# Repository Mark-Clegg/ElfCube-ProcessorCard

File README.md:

# Elf-Cube - Processor card
Simple retro computer based on the 1802 series of processors.

Holds the main CPU, 1 x 32K ROM and 2 x 32K RAM sockets.

After reset, ROM runs from 0x0000 - 0x7FFF and RAM from 0x8000 - 0xFFFF. As soon as an instruction fetch occurs from RAM, the
ROM is replaced with the second RAM chip leaving a full 64K RAM available to user programs.

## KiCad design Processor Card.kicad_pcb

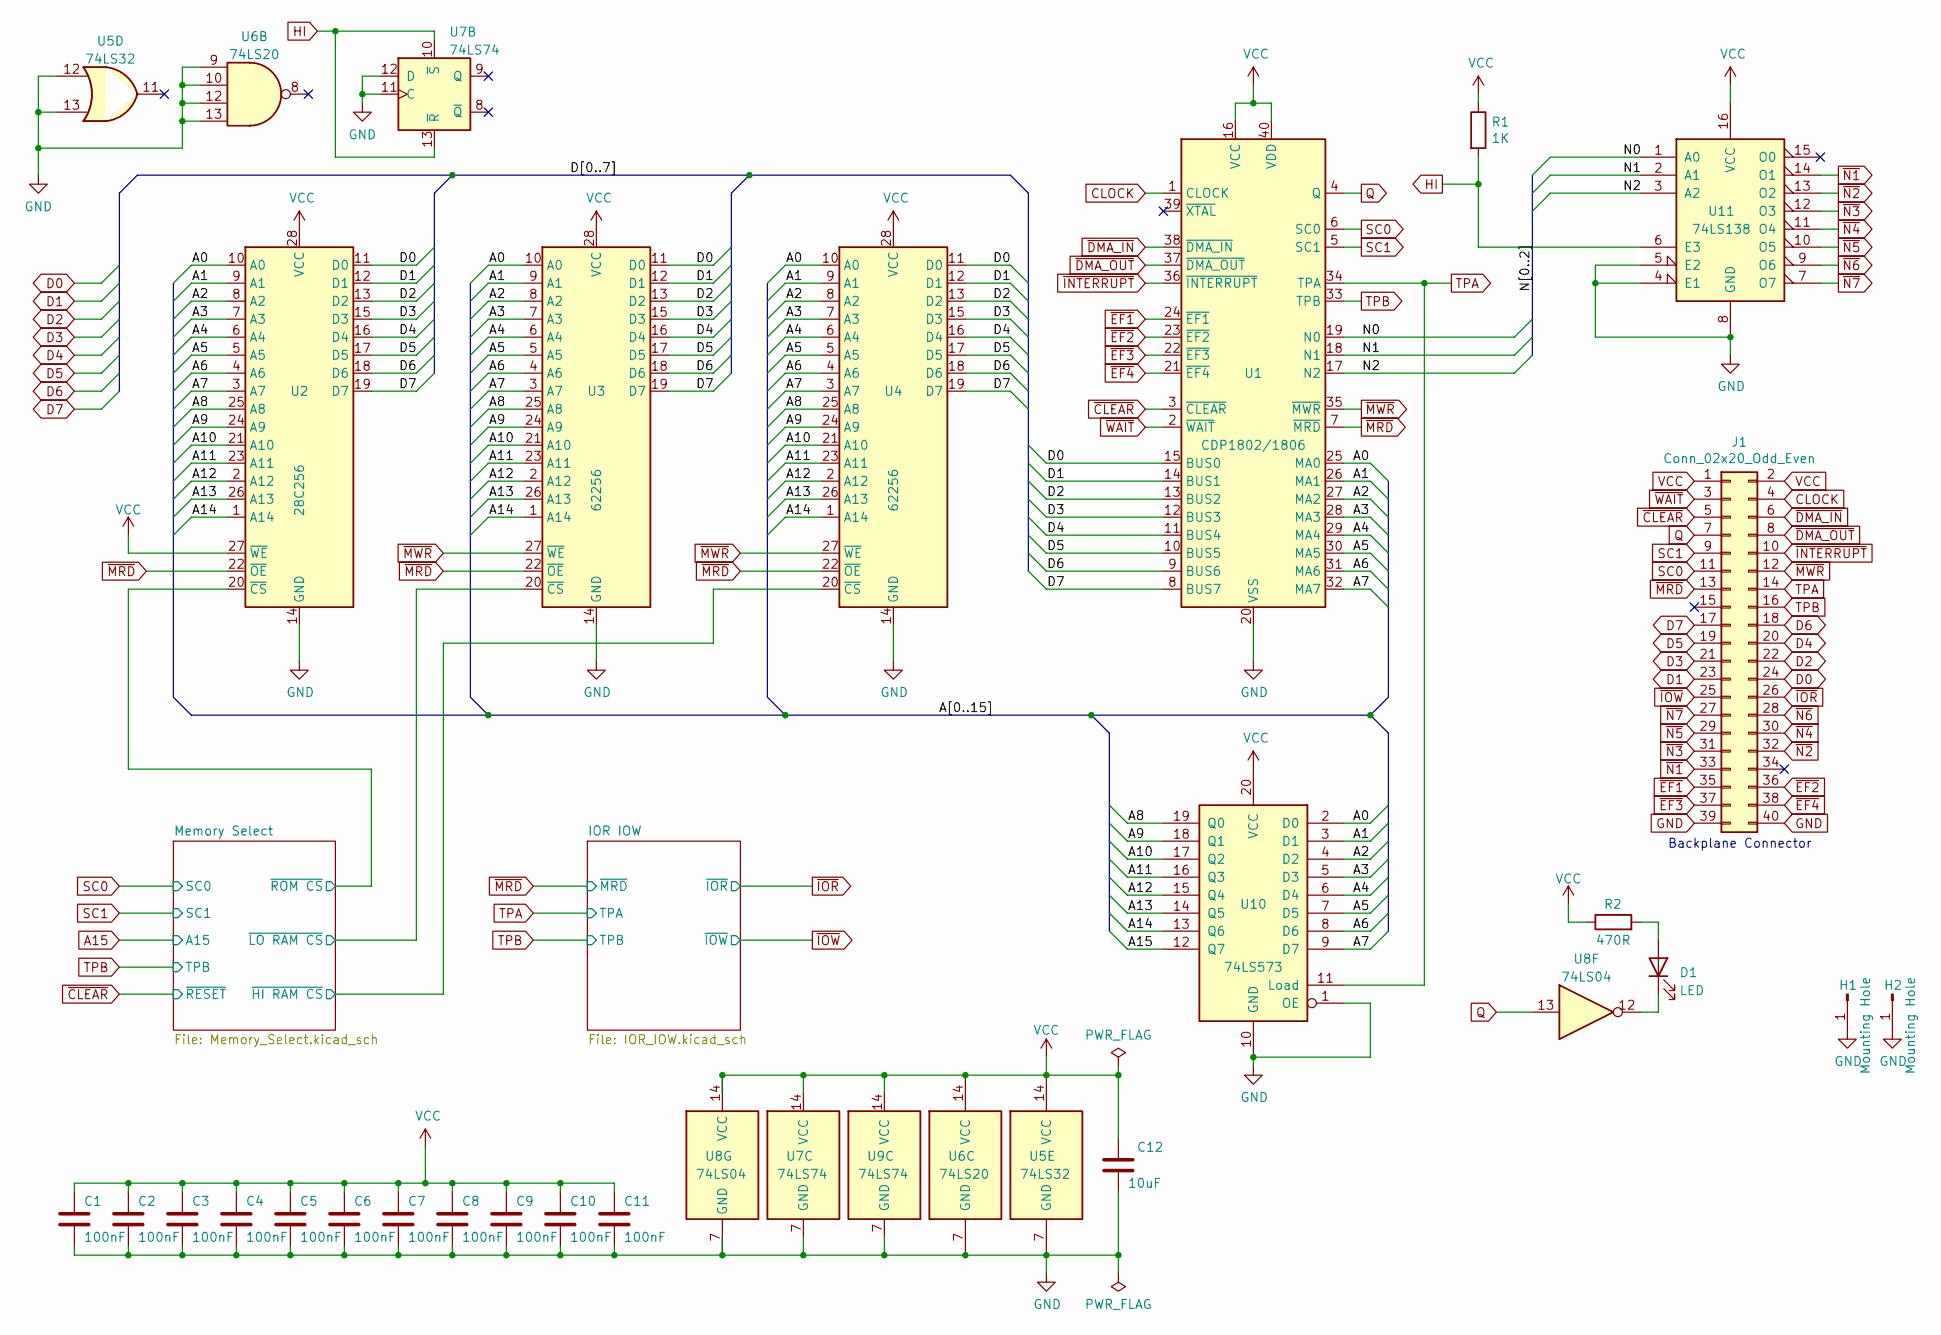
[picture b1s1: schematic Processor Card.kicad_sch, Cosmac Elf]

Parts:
C1, C2, C3, C4, C5, C6, C7, C8, C9, C10, C11: 100nF; C_Disc_D3.8mm_W2.6mm_P2.50mm
C12: 10uF; CP_Radial_D5.0mm_P2.50mm
D1: LED; LED_D3.0mm_Horizontal_O1.27mm_Z2.0mm
H1, H2: Mounting Hole; MountingHole_3.2mm_M3_Pad_Via
J1: Conn_02x20_Odd_Even; PinHeader_2x20_P2.54mm_Horizontal
R1: 1K; R_Axial_DIN0207_L6.3mm_D2.5mm_P7.62mm_Horizontal
R2: 470R; R_Axial_DIN0207_L6.3mm_D2.5mm_P7.62mm_Horizontal
U1: CDP1802/1806; DIP-40_W15.24mm_Socket
U2: 28C256; DIP-28_W15.24mm_Socket
U3, U4: 62256; DIP-28_W15.24mm_Socket
U5: 74LS32; DIP-14_W7.62mm
U6: 74LS20; DIP-14_W7.62mm
U7, U9: 74LS74; DIP-14_W7.62mm
U8: 74LS04; DIP-14_W7.62mm
U10: 74LS573; DIP-20_W7.62mm
U11: 74LS138; DIP-16_W7.62mm

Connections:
/A0: U1.25 (MA0), U2.10 (A0), U3.10 (A0), U4.10 (A0), U10.2 (D0)
/A1: U1.26 (MA1), U2.9 (A1), U3.9 (A1), U4.9 (A1), U10.3 (D1)
/A2: U1.27 (MA2), U2.8 (A2), U3.8 (A2), U4.8 (A2), U10.4 (D2)
/A3: U1.28 (MA3), U2.7 (A3), U3.7 (A3), U4.7 (A3), U10.5 (D3)
/A4: U1.29 (MA4), U2.6 (A4), U3.6 (A4), U4.6 (A4), U10.6 (D4)
/A5: U1.30 (MA5), U2.5 (A5), U3.5 (A5), U4.5 (A5), U10.7 (D5)
/A6: U1.31 (MA6), U2.4 (A6), U3.4 (A6), U4.4 (A6), U10.8 (D6)
/A7: U1.32 (MA7), U2.3 (A7), U3.3 (A7), U4.3 (A7), U10.9 (D7)
/A8: U2.25 (A8), U3.25 (A8), U4.25 (A8), U10.19 (Q0)
/A9: U2.24 (A9), U3.24 (A9), U4.24 (A9), U10.18 (Q1)
/A10: U2.21 (A10), U3.21 (A10), U4.21 (A10), U10.17 (Q2)
/A11: U2.23 (A11), U3.23 (A11), U4.23 (A11), U10.16 (Q3)
/A12: U2.2 (A12), U3.2 (A12), U4.2 (A12), U10.15 (Q4)
/A13: U2.26 (A13), U3.26 (A13), U4.26 (A13), U10.14 (Q5)
/A14: U2.1 (A14), U3.1 (A14), U4.1 (A14), U10.13 (Q6)
/Memory Select/~HI RAM CS: U4.20 (~CS); also elsewhere on the board
/Memory Select/~LO RAM CS: U3.20 (~CS); also elsewhere on the board
/Memory Select/~ROM CS: U2.20 (~CS); also elsewhere on the board
/N0: U1.19 (N0), U11.1 (A0)
/N1: U1.18 (N1), U11.2 (A1)
/N2: U1.17 (N2), U11.3 (A2)
A15: U10.12 (Q7); also elsewhere on the board
CLOCK: J1.4, U1.1 (CLOCK)
D0: J1.24, U1.15 (BUS0), U2.11 (D0), U3.11 (D0), U4.11 (D0)
D1: J1.23, U1.14 (BUS1), U2.12 (D1), U3.12 (D1), U4.12 (D1)
D2: J1.22, U1.13 (BUS2), U2.13 (D2), U3.13 (D2), U4.13 (D2)
D3: J1.21, U1.12 (BUS3), U2.15 (D3), U3.15 (D3), U4.15 (D3)
D4: J1.20, U1.11 (BUS4), U2.16 (D4), U3.16 (D4), U4.16 (D4)
D5: J1.19, U1.10 (BUS5), U2.17 (D5), U3.17 (D5), U4.17 (D5)
D6: J1.18, U1.9 (BUS6), U2.18 (D6), U3.18 (D6), U4.18 (D6)
D7: J1.17, U1.8 (BUS7), U2.19 (D7), U3.19 (D7), U4.19 (D7)
GND: C1.2, C2.2, C3.2, C4.2, C5.2, C6.2, C7.2, C8.2, C9.2, C10.2, C11.2, C12.2, H1.1, H2.1, J1.39, J1.40, U1.20 (VSS), U2.14 (GND), U3.14 (GND), U4.14 (GND), U5.7 (GND), U5.12, U5.13, U6.7 (GND), U6.9, U6.10, U6.12, U6.13, U7.7 (GND), U7.11 (C), U7.12 (D), U8.7 (GND), U9.7 (GND), U10.1 (OE), U10.10 (GND), U11.4 (E1), U11.5 (E2), U11.8 (GND); also elsewhere on the board
HI: R1.2, U7.10 (~S), U7.13 (~R), U11.6 (E3); also elsewhere on the board
unnamed: D1.1 (K), U8.12
unnamed: D1.2 (A), R2.2
Q: J1.7, U1.4 (Q), U8.13
SC0: J1.11, U1.6 (SC0); also elsewhere on the board
SC1: J1.9, U1.5 (SC1); also elsewhere on the board
TPA: J1.14, U1.34 (TPA), U10.11 (Load); also elsewhere on the board
TPB: J1.16, U1.33 (TPB); also elsewhere on the board
VCC: C1.1, C2.1, C3.1, C4.1, C5.1, C6.1, C7.1, C8.1, C9.1, C10.1, C11.1, C12.1, J1.1, J1.2, R1.1, R2.1, U1.16 (VCC), U1.40 (VDD), U2.27 (~WE), U2.28 (VCC), U3.28 (VCC), U4.28 (VCC), U5.14 (VCC), U6.14 (VCC), U7.14 (VCC), U8.14 (VCC), U9.14 (VCC), U10.20 (VCC), U11.16 (VCC)
~CLEAR: J1.5, U1.3 (~CLEAR); also elsewhere on the board
~DMA_IN: J1.6, U1.38 (~DMA_IN)
~DMA_OUT: J1.8, U1.37 (~DMA_OUT)
~EF1: J1.35, U1.24 (~EF1)
~EF2: J1.36, U1.23 (~EF2)
~EF3: J1.37, U1.22 (~EF3)
~EF4: J1.38, U1.21 (~EF4)
~INTERRUPT: J1.10, U1.36 (~INTERRUPT)
~IOR: J1.26; also elsewhere on the board
~IOW: J1.25; also elsewhere on the board
~MRD: J1.13, U1.7 (~MRD), U2.22 (~OE), U3.22 (~OE), U4.22 (~OE); also elsewhere on the board
~MWR: J1.12, U1.35 (~MWR), U3.27 (~WE), U4.27 (~WE)
~N1: J1.33, U11.14 (O1)
~N2: J1.32, U11.13 (O2)
~N3: J1.31, U11.12 (O3)
~N4: J1.30, U11.11 (O4)
~N5: J1.29, U11.10 (O5)
~N6: J1.28, U11.9 (O6)
~N7: J1.27, U11.7 (O7)
~WAIT: J1.3, U1.2 (~WAIT)

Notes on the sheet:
Backplane Connector

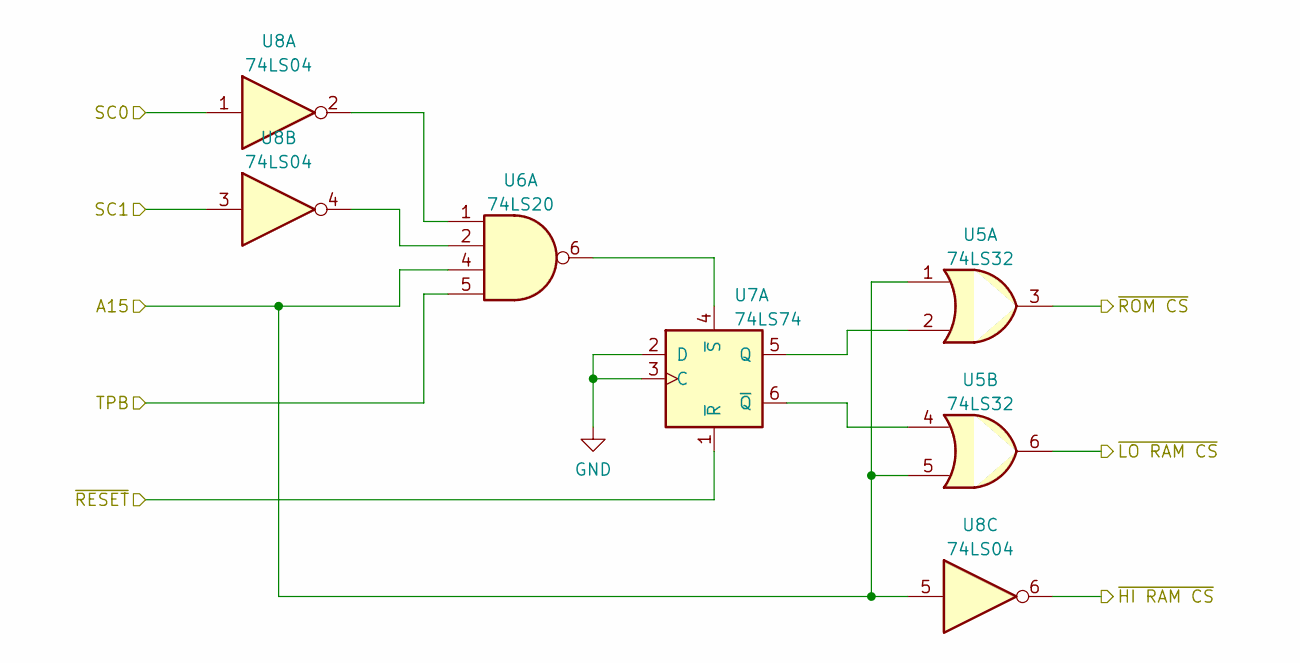
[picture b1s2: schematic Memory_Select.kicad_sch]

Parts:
U5: 74LS32; DIP-14_W7.62mm
U6: 74LS20; DIP-14_W7.62mm
U7: 74LS74; DIP-14_W7.62mm
U8: 74LS04; DIP-14_W7.62mm

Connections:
/Memory Select/~HI RAM CS: U8.6; also elsewhere on the board
/Memory Select/~LO RAM CS: U5.6; also elsewhere on the board
/Memory Select/~ROM CS: U5.3; also elsewhere on the board
A15: U5.1, U5.5, U6.4, U8.5; also elsewhere on the board
GND: U7.2 (D), U7.3 (C); also elsewhere on the board
unnamed: U5.2, U7.5 (Q)
unnamed: U5.4, U7.6 (~Q)
unnamed: U6.1, U8.2
unnamed: U6.2, U8.4
unnamed: U6.6, U7.4 (~S)
SC0: U8.1; also elsewhere on the board
SC1: U8.3; also elsewhere on the board
TPB: U6.5; also elsewhere on the board
~CLEAR: U7.1 (~R); also elsewhere on the board

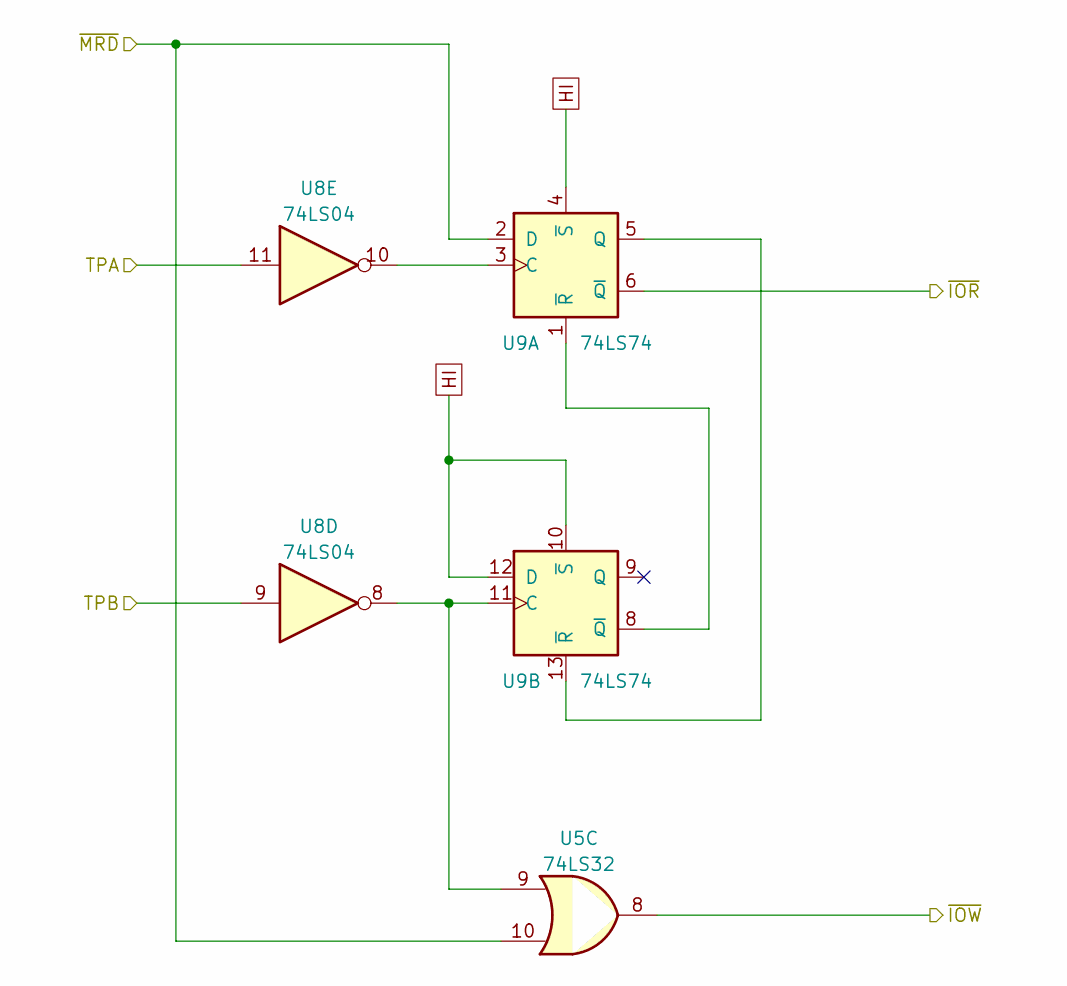
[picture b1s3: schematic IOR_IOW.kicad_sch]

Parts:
U5: 74LS32; DIP-14_W7.62mm
U8: 74LS04; DIP-14_W7.62mm
U9: 74LS74; DIP-14_W7.62mm

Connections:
HI: U9.4 (~S), U9.10 (~S), U9.12 (D); also elsewhere on the board
unnamed: U5.9, U8.8, U9.11 (C)
unnamed: U8.10, U9.3 (C)
unnamed: U9.1 (~R), U9.8 (~Q)
unnamed: U9.5 (Q), U9.13 (~R)
TPA: U8.11; also elsewhere on the board
TPB: U8.9; also elsewhere on the board
~IOR: U9.6 (~Q); also elsewhere on the board
~IOW: U5.8; also elsewhere on the board
~MRD: U5.10, U9.2 (D); also elsewhere on the board

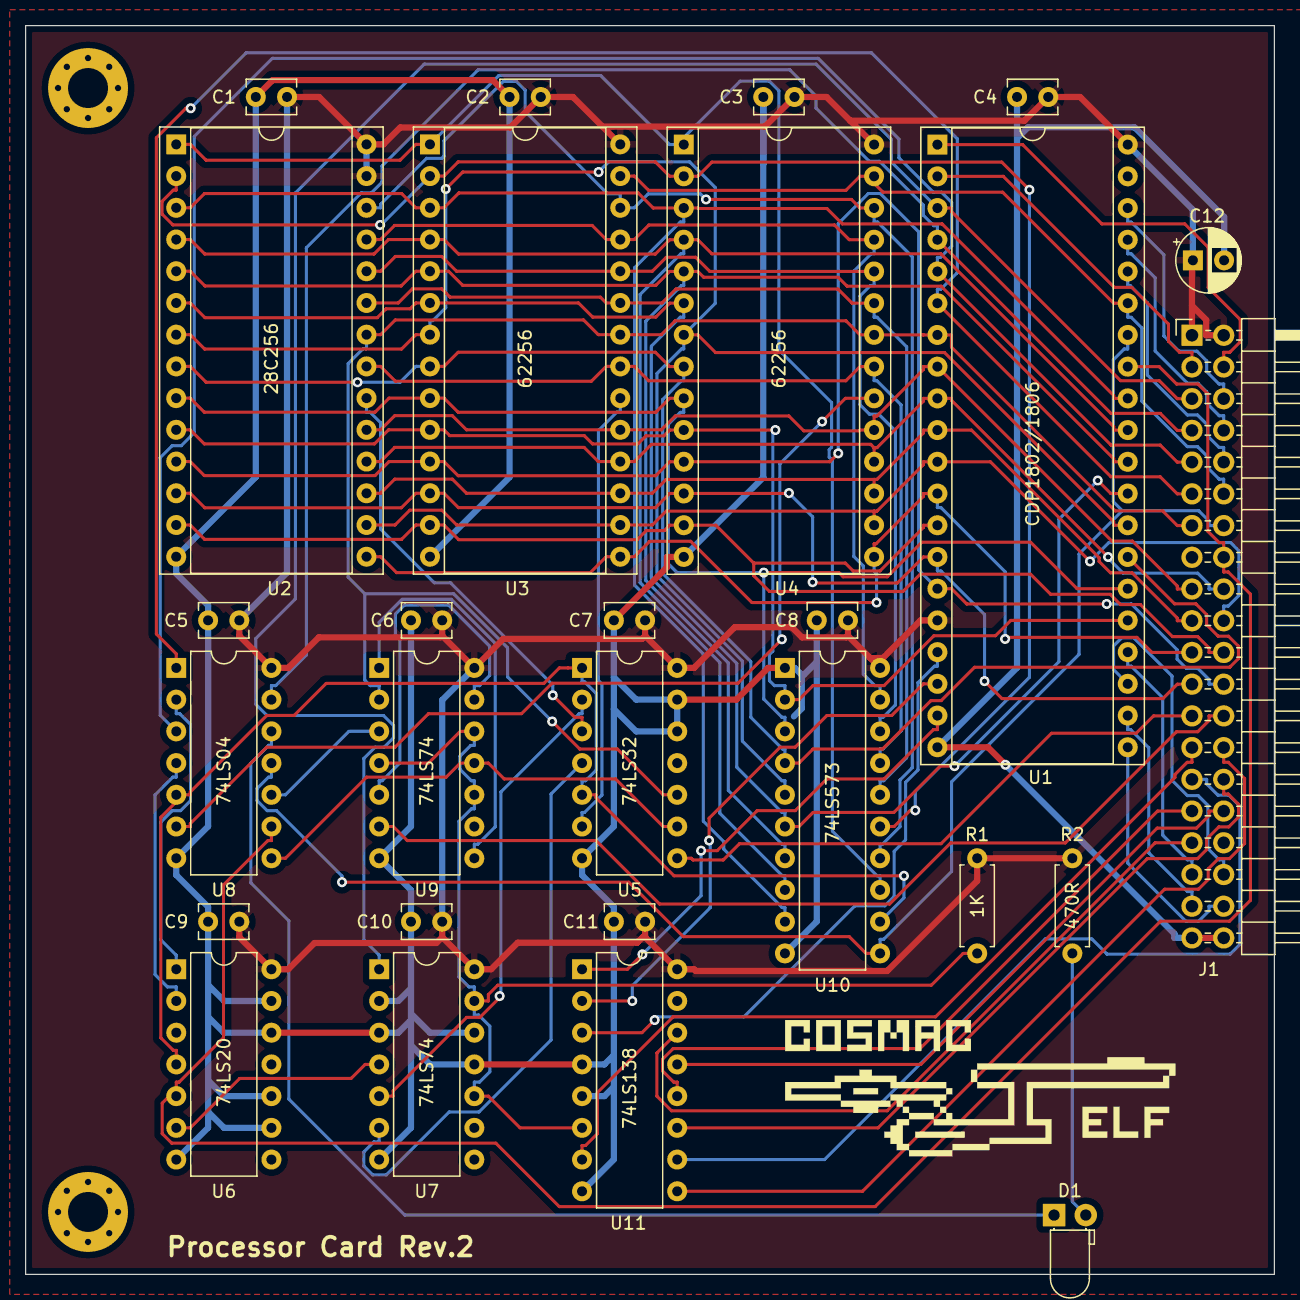
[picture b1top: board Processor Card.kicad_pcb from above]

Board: 2 copper layers, 100.0 x 100.0 mm, 29 parts (0 on the bottom side), 70 nets.

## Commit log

2021-11-06 Rev 1.0
2021-11-06 Added Gate Delay to IO Decode
2021-11-06 Added README.md
2021-11-08 Updated Wiki
2021-11-30 Sync
2023-02-21 Revision 2
2023-03-02 Fix PCB / Schematic mismatch
2023-03-03 Finalised layout
2023-03-17 Rev 2
2023-03-17 Updated Docs
